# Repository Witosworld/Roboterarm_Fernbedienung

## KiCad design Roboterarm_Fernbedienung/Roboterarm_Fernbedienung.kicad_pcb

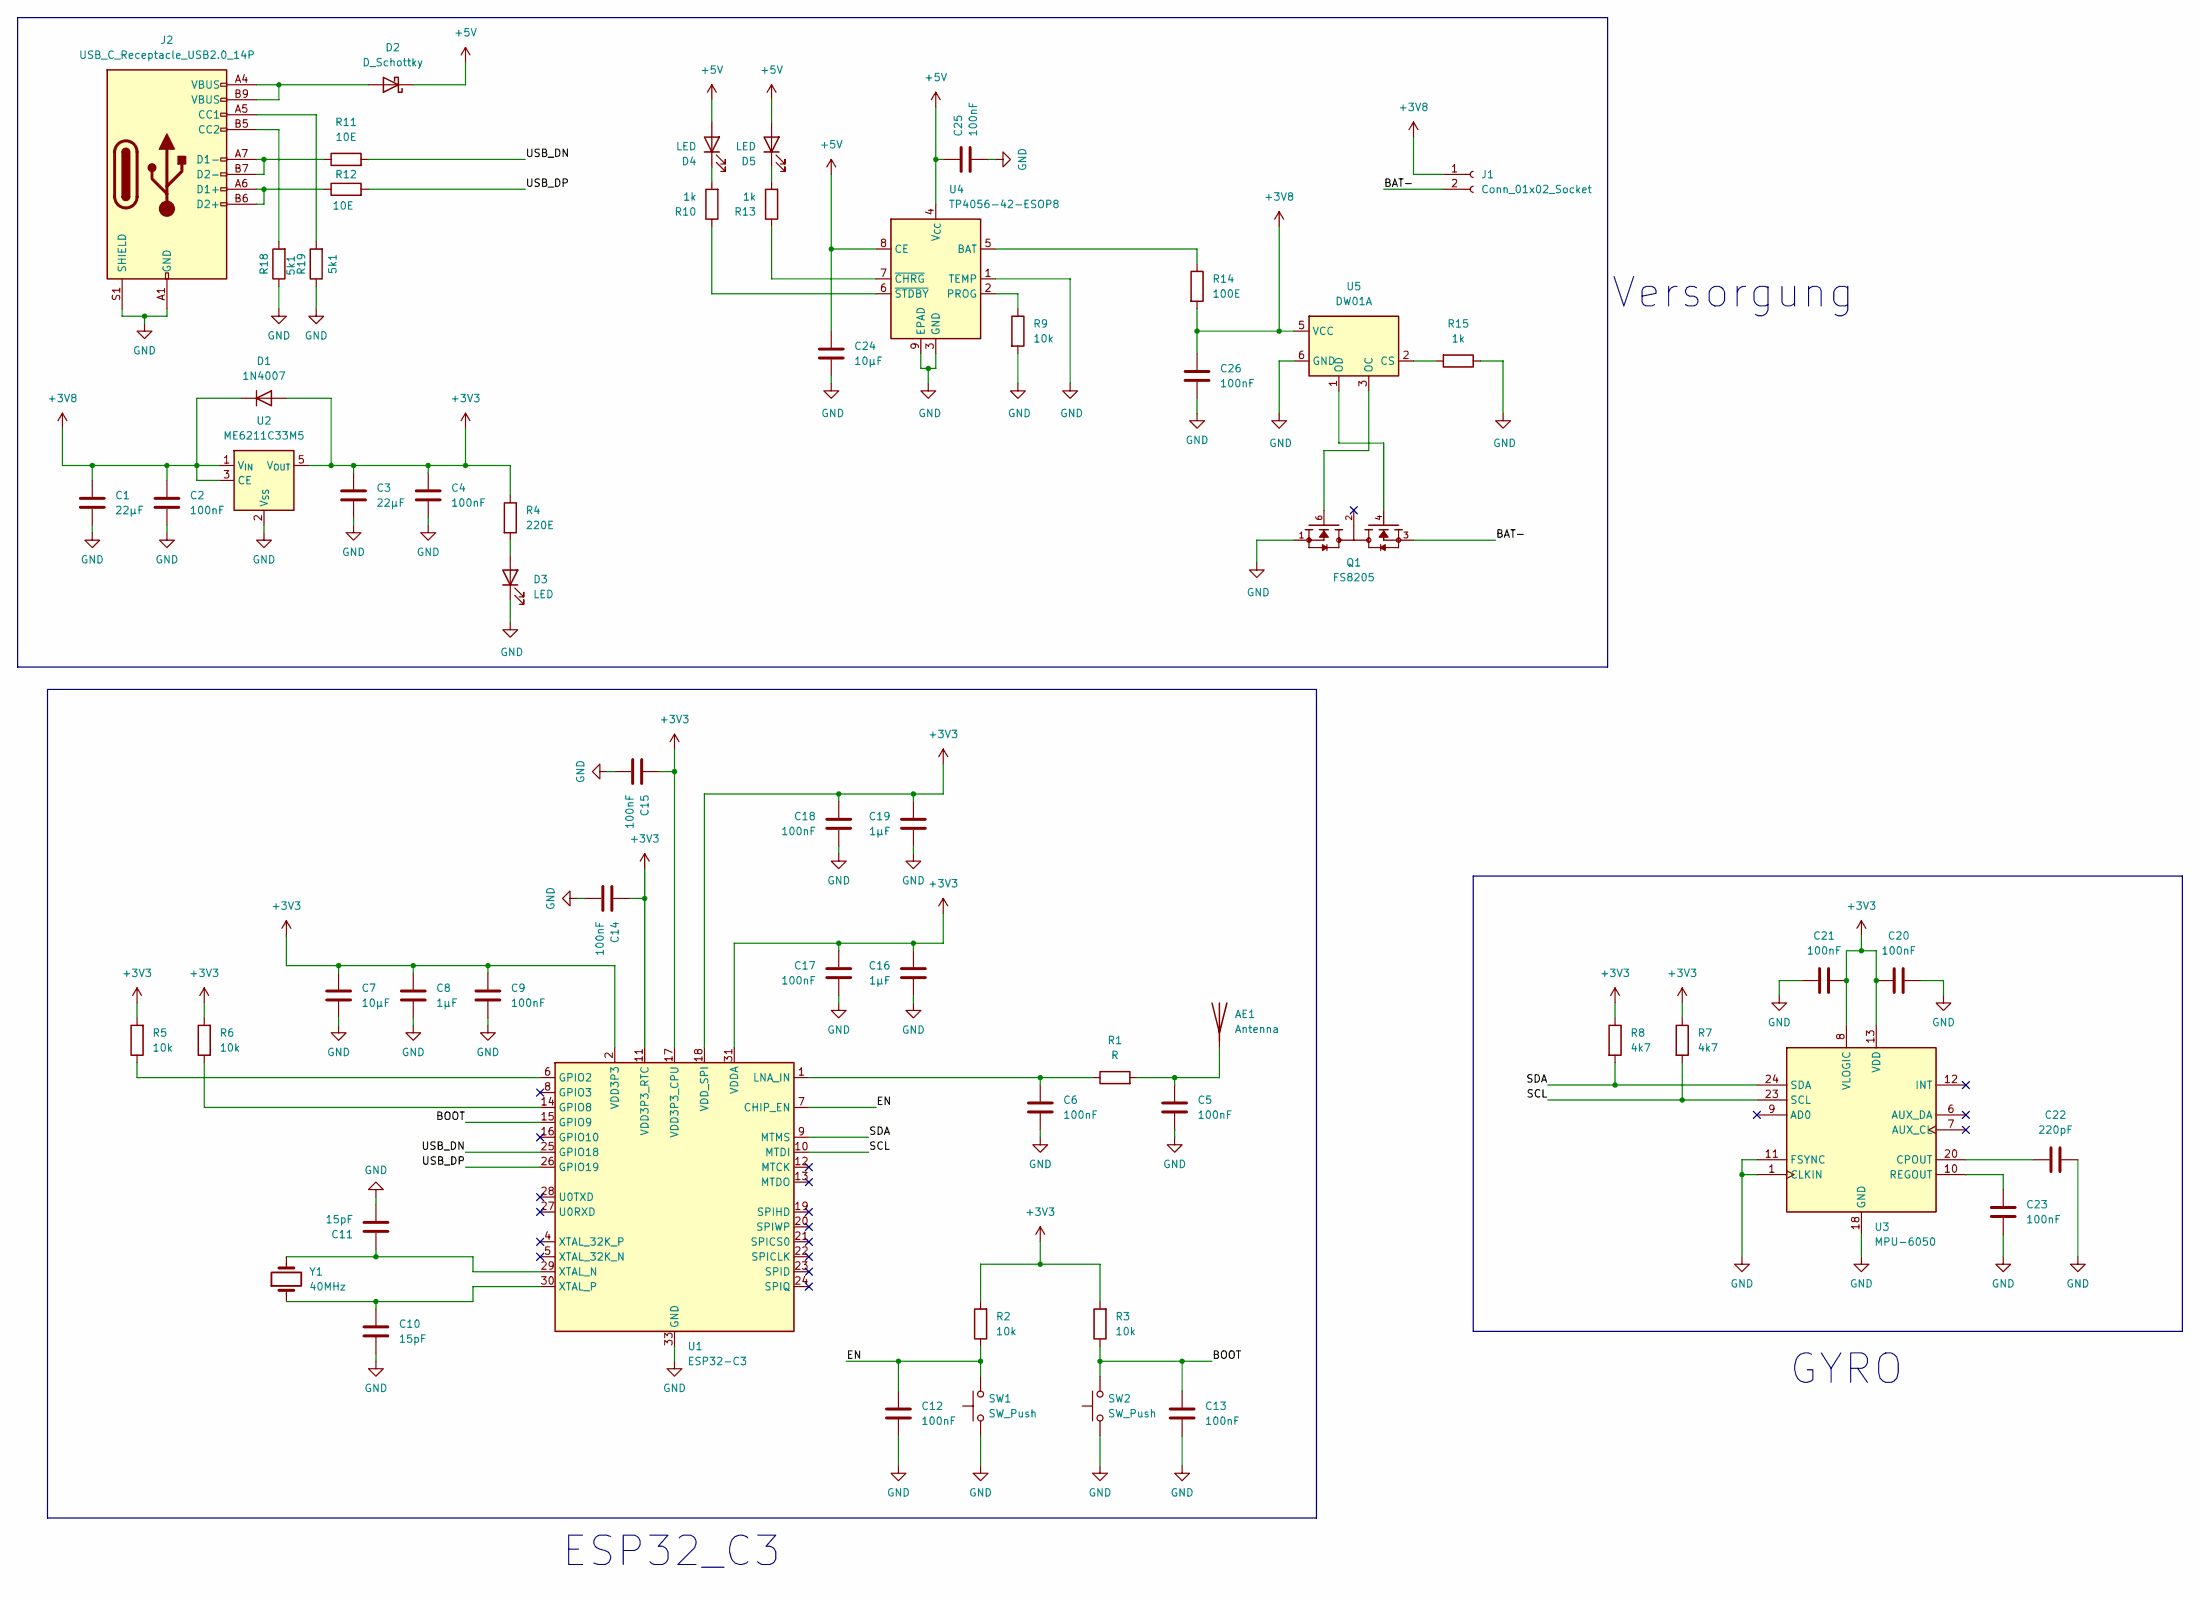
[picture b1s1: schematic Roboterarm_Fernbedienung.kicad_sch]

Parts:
AE1: Antenna
C1, C3: 22µF; C_0805_2012Metric
C2, C4, C5, C6, C9, C12, C13, C14, C15, C17, C18, C20, C21, C23, C25, C26: 100nF; C_0603_1608Metric
C7: 10µF; C_0805_2012Metric
C8, C16, C19: 1µF; C_0603_1608Metric
C10, C11: 15pF; C_0603_1608Metric
C22: 220pF; C_0603_1608Metric
C24: 10µF; C_0603_1608Metric
D1: 1N4007; D_DO-41_SOD81_P10.16mm_Horizontal
D2: D_Schottky; D_SOD-323
D3, D4, D5: LED; LED_0603_1608Metric
J1: Conn_01x02_Socket; Molex_KK-254_AE-6410-02A_1x02_P2.54mm_Vertical
J2: USB_C_Receptacle_USB2.0_14P; USB_C_Receptacle_HRO_TYPE-C-31-M-12
Q1: FS8205; SOT95P280X145-6N; PARTREV 1.9
R1: R; R_0603_1608Metric
R2, R3, R5, R6, R9: 10k; R_0603_1608Metric
R4: 220E; R_0603_1608Metric
R7, R8: 4k7; R_0603_1608Metric
R10, R13, R15: 1k; R_0603_1608Metric
R11, R12: 10E; R_0603_1608Metric
R14: 100E; R_0603_1608Metric
R18, R19: 5k1; R_0402_1005Metric
SW1, SW2: SW_Push; SW_SPST_B3U-1000P-B
U1: ESP32-C3; QFN-32-1EP_5x5mm_P0.5mm_EP3.7x3.7mm
U2: ME6211C33M5; SOT-23-5
U3: MPU-6050; InvenSense_QFN-24_4x4mm_P0.5mm
U4: TP4056-42-ESOP8; SOIC-8-1EP_3.9x4.9mm_P1.27mm_EP2.41x3.3mm_ThermalVias
U5: DW01A; SOT-23-6
Y1: 40MHz; Oscillator_SMD_Abracon_ASE-4Pin_3.2x2.5mm

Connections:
+3V3: C3.1, C4.1, C7.1, C8.1, C9.1, C14.1, C15.1, C16.1, C17.1, C18.1, C19.1, C20.1, C21.2, D1.2 (A), R2.2, R3.2, R4.1, R5.2, R6.2, R7.1, R8.1, U1.2 (VDD3P3), U1.3 (VDD3P3), U1.11 (VDD3P3_RTC), U1.17 (VDD3P3_CPU), U1.18 (VDD_SPI), U1.31 (VDDA), U1.32 (VDDA), U2.5 (V_{OUT}), U3.8 (VLOGIC), U3.13 (VDD)
+3V8: C1.1, C2.1, C26.1, D1.1 (K), J1.1, R14.2, U2.1 (V_{IN}), U2.3 (CE), U5.5 (VCC)
+5V: C24.1, C25.1, D2.1 (K), D4.2 (A), D5.2 (A), U4.4 (V_{CC}), U4.8 (CE)
/BAT-: J1.2, Q1.3
/BOOT: C13.1, R3.1, SW2.2, U1.15 (GPIO9)
/EN: C12.1, R2.1, SW1.2, U1.7 (CHIP_EN)
/SCL: R7.2, U1.10 (MTDI), U3.23 (SCL)
/SDA: R8.2, U1.9 (MTMS), U3.24 (SDA)
/USB_DN: R11.2, U1.25 (GPIO18)
/USB_DP: R12.2, U1.26 (GPIO19)
GND: C1.2, C2.2, C3.2, C4.2, C5.2, C6.2, C7.2, C8.2, C9.2, C10.2, C11.2, C12.2, C13.2, C14.2, C15.2, C16.2, C17.2, C18.2, C19.2, C20.2, C21.1, C22.2, C23.1, C24.2, C25.2, C26.2, D3.1 (K), J2.A1 (GND), J2.A12 (GND), J2.B1 (GND), J2.B12 (GND), J2.S1 (SHIELD), Q1.1, R9.2, R15.1, R18.1, R19.1, SW1.1, SW2.1, U1.33 (GND), U2.2 (V_{SS}), U3.1 (CLKIN), U3.11 (FSYNC), U3.18 (GND), U4.1 (TEMP), U4.3 (GND), U4.9 (EPAD), U5.6 (GND)
unnamed: AE1.1, C5.1, R1.2
unnamed: D2.2 (A), J2.A4 (VBUS), J2.A9 (VBUS), J2.B4 (VBUS), J2.B9 (VBUS)
unnamed: D3.2 (A), R4.2
unnamed: D4.1 (K), R10.2
unnamed: D5.1 (K), R13.2
unnamed: J2.A5 (CC1), R19.2
unnamed: J2.B5 (CC2), R18.2
unnamed: J2.A6 (D1+), J2.B6 (D2+), R12.1
unnamed: J2.A7 (D1-), J2.B7 (D2-), R11.1
unnamed: Q1.2, Q1.5
unnamed: R5.1, U1.6 (GPIO2)
unnamed: R6.1, U1.14 (GPIO8)
unnamed: C6.1, R1.1, U1.1 (LNA_IN)
unnamed: C11.1, U1.29 (XTAL_N), Y1.2
unnamed: C10.1, U1.30 (XTAL_P), Y1.1
unnamed: C22.1, U3.20 (CPOUT)
unnamed: C23.2, U3.10 (REGOUT)
unnamed: R14.1, U4.5 (BAT)
unnamed: R9.1, U4.2 (PROG)
unnamed: R13.1, U4.7 (~CHRG)
unnamed: R10.1, U4.6 (~STDBY)
unnamed: R15.2, U5.2 (CS)
unnamed: Q1.6, U5.3 (OC)
unnamed: Q1.4, U5.1 (OD)

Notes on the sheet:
Versorgung
GYRO
ESP32_C3

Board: 2 copper layers, 58 parts (0 on the bottom side), 31 nets, no tracks yet.
